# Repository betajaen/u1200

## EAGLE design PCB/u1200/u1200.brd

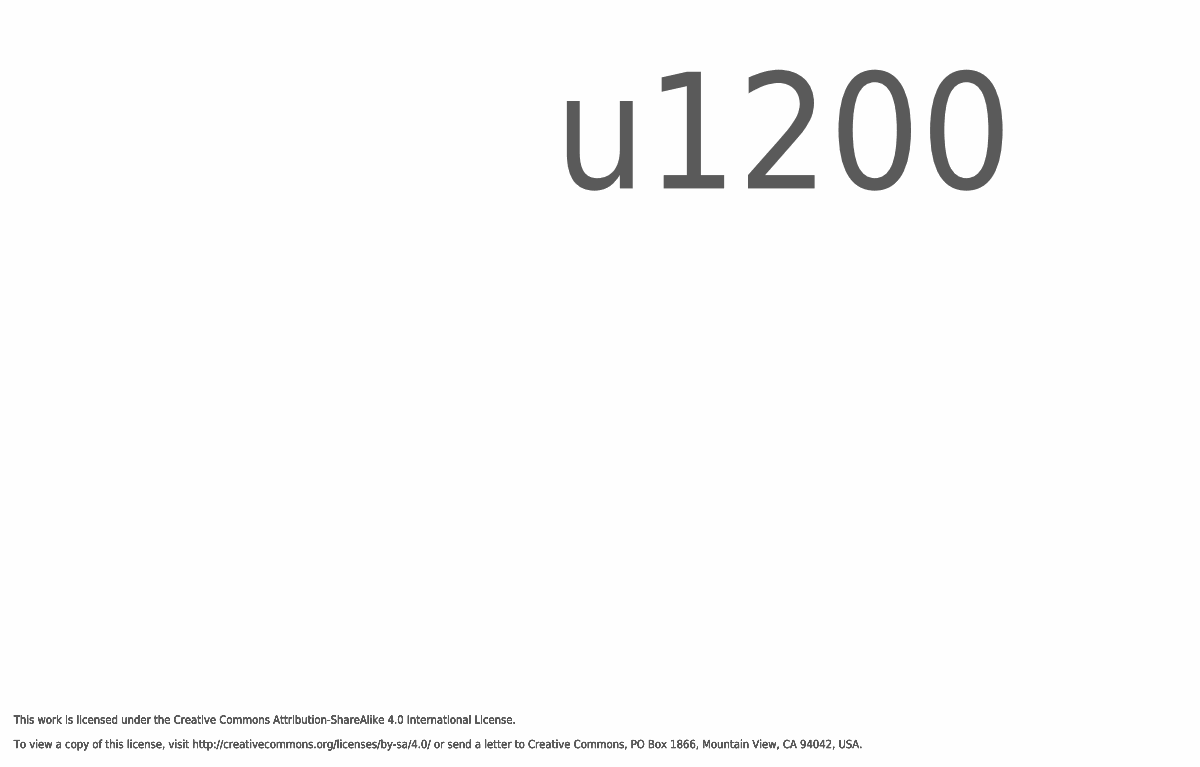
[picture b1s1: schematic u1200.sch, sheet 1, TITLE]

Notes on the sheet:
u1200
This work is licensed under the Creative Commons Attribution-ShareAlike 4.0 International License. To view a copy of this license, visit http://creativecommons.org/licenses/by-sa/4.0/ or send a letter to Creative Commons, PO Box 1866, Mountain View, CA 94042, USA.

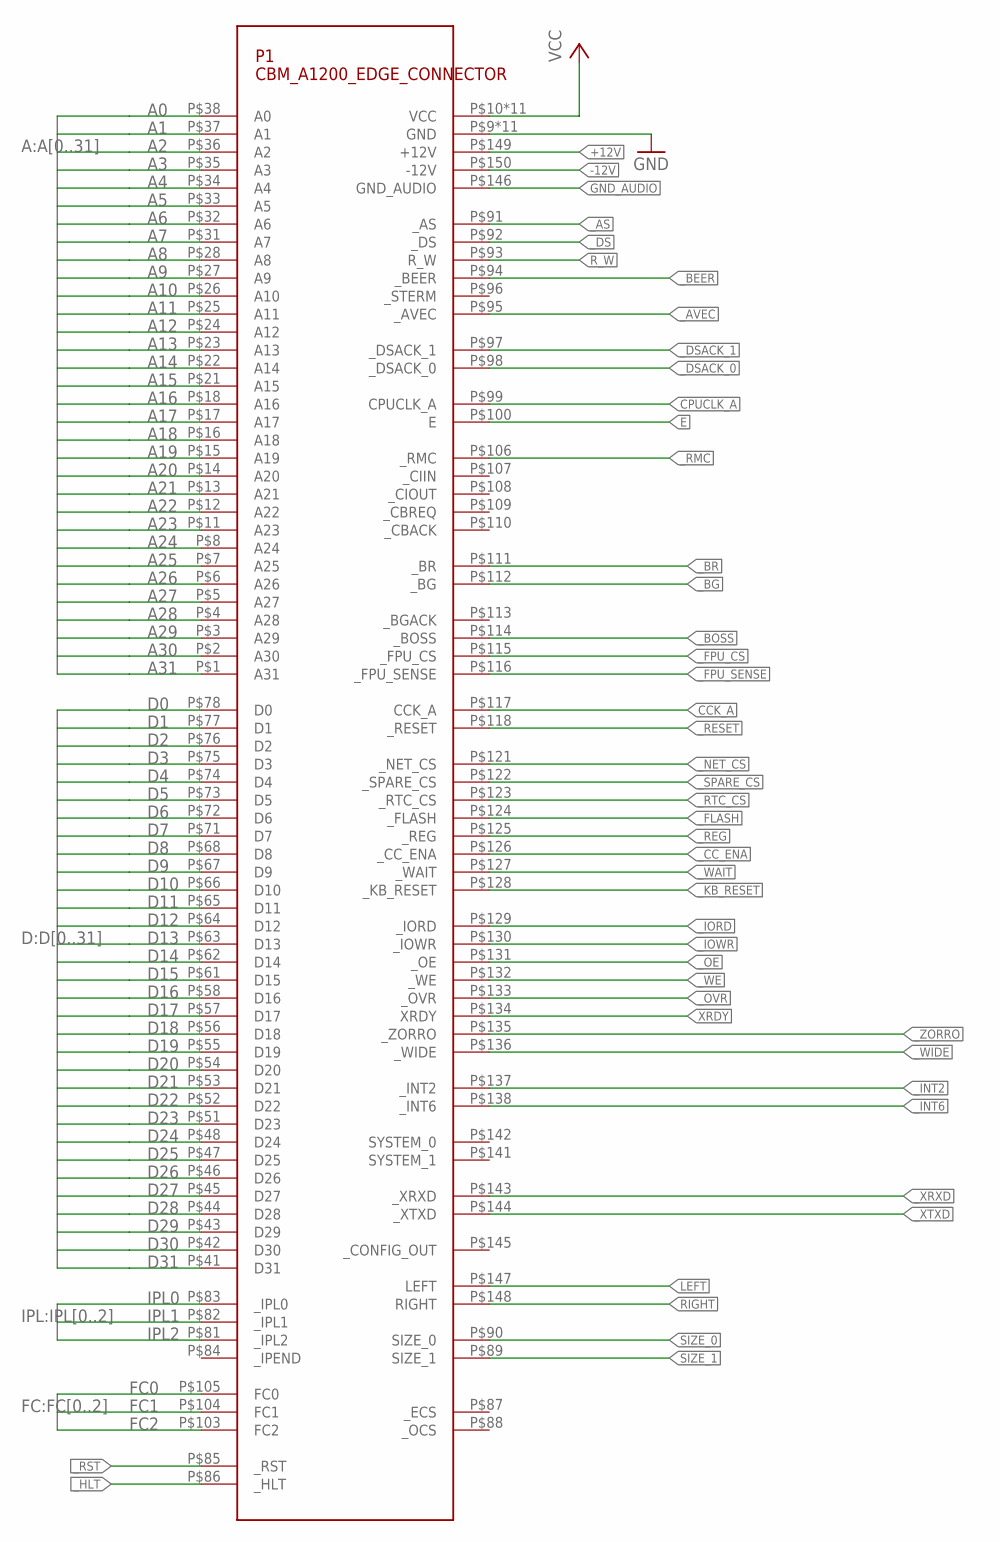
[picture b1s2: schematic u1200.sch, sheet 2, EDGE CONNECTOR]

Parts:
P1: CBM_A1200_EDGE_CONNECTOR; CBM_A1200_EDGE_CONNECTOR_150P

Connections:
+12V: P1.P$149 (+12V); also elsewhere on the board
-12V: P1.P$150 (-12V); also elsewhere on the board
A0: P1.P$38 (A0); also elsewhere on the board
A1: P1.P$37 (A1); also elsewhere on the board
A2: P1.P$36 (A2); also elsewhere on the board
A3: P1.P$35 (A3); also elsewhere on the board
A4: P1.P$34 (A4); also elsewhere on the board
A5: P1.P$33 (A5); also elsewhere on the board
A6: P1.P$32 (A6); also elsewhere on the board
A7: P1.P$31 (A7); also elsewhere on the board
A8: P1.P$28 (A8); also elsewhere on the board
A9: P1.P$27 (A9); also elsewhere on the board
A10: P1.P$26 (A10); also elsewhere on the board
A11: P1.P$25 (A11); also elsewhere on the board
A12: P1.P$24 (A12); also elsewhere on the board
A13: P1.P$23 (A13); also elsewhere on the board
A14: P1.P$22 (A14); also elsewhere on the board
A15: P1.P$21 (A15); also elsewhere on the board
A16: P1.P$18 (A16); also elsewhere on the board
A17: P1.P$17 (A17); also elsewhere on the board
A18: P1.P$16 (A18); also elsewhere on the board
A19: P1.P$15 (A19); also elsewhere on the board
A20: P1.P$14 (A20); also elsewhere on the board
A21: P1.P$13 (A21)
A22: P1.P$12 (A22)
A23: P1.P$11 (A23)
A24: P1.P$8 (A24)
A25: P1.P$7 (A25)
A26: P1.P$6 (A26)
A27: P1.P$5 (A27)
A28: P1.P$4 (A28)
A29: P1.P$3 (A29)
A30: P1.P$2 (A30)
A31: P1.P$1 (A31)
CCK_A: P1.P$117 (CCK_A); also elsewhere on the board
CPUCLK_A: P1.P$99 (CPUCLK_A); also elsewhere on the board
D0: P1.P$78 (D0); also elsewhere on the board
D1: P1.P$77 (D1); also elsewhere on the board
D2: P1.P$76 (D2); also elsewhere on the board
D3: P1.P$75 (D3); also elsewhere on the board
D4: P1.P$74 (D4); also elsewhere on the board
D5: P1.P$73 (D5); also elsewhere on the board
D6: P1.P$72 (D6); also elsewhere on the board
D7: P1.P$71 (D7); also elsewhere on the board
D8: P1.P$68 (D8); also elsewhere on the board
D9: P1.P$67 (D9); also elsewhere on the board
D10: P1.P$66 (D10); also elsewhere on the board
D11: P1.P$65 (D11); also elsewhere on the board
D12: P1.P$64 (D12); also elsewhere on the board
D13: P1.P$63 (D13); also elsewhere on the board
D14: P1.P$62 (D14); also elsewhere on the board
D15: P1.P$61 (D15); also elsewhere on the board
D16: P1.P$58 (D16); also elsewhere on the board
D17: P1.P$57 (D17); also elsewhere on the board
D18: P1.P$56 (D18); also elsewhere on the board
D19: P1.P$55 (D19); also elsewhere on the board
D20: P1.P$54 (D20); also elsewhere on the board
D21: P1.P$53 (D21); also elsewhere on the board
D22: P1.P$52 (D22); also elsewhere on the board
D23: P1.P$51 (D23); also elsewhere on the board
D24: P1.P$48 (D24); also elsewhere on the board
D25: P1.P$47 (D25); also elsewhere on the board
D26: P1.P$46 (D26); also elsewhere on the board
D27: P1.P$45 (D27); also elsewhere on the board
D28: P1.P$44 (D28); also elsewhere on the board
D29: P1.P$43 (D29); also elsewhere on the board
D30: P1.P$42 (D30); also elsewhere on the board
D31: P1.P$41 (D31); also elsewhere on the board
E: P1.P$100 (E)
FC0: P1.P$105 (FC0); also elsewhere on the board
FC1: P1.P$104 (FC1); also elsewhere on the board
FC2: P1.P$103 (FC2); also elsewhere on the board
GND: P1.P$9 (GND), P1.P$19 (GND), P1.P$29 (GND), P1.P$39 (GND), P1.P$49 (GND), P1.P$59 (GND), P1.P$69 (GND), P1.P$79 (GND), P1.P$101 (GND), P1.P$119 (GND), P1.P$139 (GND); also elsewhere on the board
GND_AUDIO: P1.P$146 (GND_AUDIO)
IPL0: P1.P$83 (_IPL0); also elsewhere on the board
IPL1: P1.P$82 (_IPL1); also elsewhere on the board
IPL2: P1.P$81 (_IPL2); also elsewhere on the board
LEFT: P1.P$147 (LEFT)
RIGHT: P1.P$148 (RIGHT)
R_W: P1.P$93 (R_W); also elsewhere on the board
SIZE_0: P1.P$90 (SIZE_0); also elsewhere on the board
SIZE_1: P1.P$89 (SIZE_1); also elsewhere on the board
VCC: P1.P$10 (VCC), P1.P$20 (VCC), P1.P$30 (VCC), P1.P$40 (VCC), P1.P$50 (VCC), P1.P$60 (VCC), P1.P$70 (VCC), P1.P$80 (VCC), P1.P$102 (VCC), P1.P$120 (VCC), P1.P$140 (VCC); also elsewhere on the board
XRDY: P1.P$134 (XRDY); also elsewhere on the board
_AS: P1.P$91 (_AS); also elsewhere on the board
_AVEC: P1.P$95 (_AVEC); also elsewhere on the board
_BEER: P1.P$94 (_BEER); also elsewhere on the board
_BG: P1.P$112 (_BG)
_BOSS: P1.P$114 (_BOSS)
_BR: P1.P$111 (_BR); also elsewhere on the board
_CC_ENA: P1.P$126 (_CC_ENA)
_DS: P1.P$92 (_DS); also elsewhere on the board
_DSACK_0: P1.P$98 (_DSACK_0); also elsewhere on the board
_DSACK_1: P1.P$97 (_DSACK_1); also elsewhere on the board
_FLASH: P1.P$124 (_FLASH)
_FPU_CS: P1.P$115 (_FPU_CS)
_FPU_SENSE: P1.P$116 (_FPU_SENSE)
_HLT: P1.P$86 (_HLT); also elsewhere on the board
_INT2: P1.P$137 (_INT2); also elsewhere on the board
_INT6: P1.P$138 (_INT6); also elsewhere on the board
_IORD: P1.P$129 (_IORD)
_IOWR: P1.P$130 (_IOWR)
_KB_RESET: P1.P$128 (_KB_RESET)
_NET_CS: P1.P$121 (_NET_CS)
_OE: P1.P$131 (_OE); also elsewhere on the board
_OVR: P1.P$133 (_OVR); also elsewhere on the board
_REG: P1.P$125 (_REG)
_RESET: P1.P$118 (_RESET)
_RMC: P1.P$106 (_RMC)
_RST: P1.P$85 (_RST); also elsewhere on the board
_RTC_CS: P1.P$123 (_RTC_CS)
_SPARE_CS: P1.P$122 (_SPARE_CS)
_WAIT: P1.P$127 (_WAIT)
_WE: P1.P$132 (_WE); also elsewhere on the board
_WIDE: P1.P$136 (_WIDE); also elsewhere on the board
_XRXD: P1.P$143 (_XRXD)
_XTXD: P1.P$144 (_XTXD)
_ZORRO: P1.P$135 (_ZORRO); also elsewhere on the board

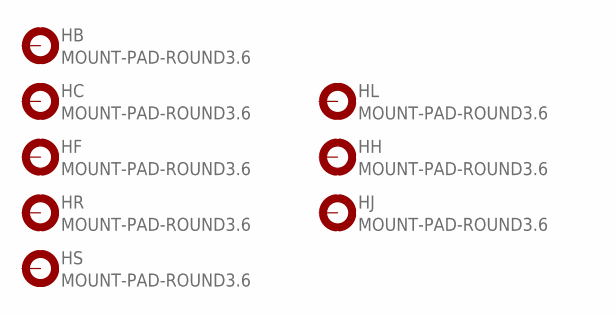
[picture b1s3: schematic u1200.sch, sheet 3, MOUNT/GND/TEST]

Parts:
HB: MOUNT-PAD-ROUND3.6; 3,6-PAD
HC: MOUNT-PAD-ROUND3.6; 3,6-PAD
HF: MOUNT-PAD-ROUND3.6; 3,6-PAD
HH: MOUNT-PAD-ROUND3.6; 3,6-PAD
HJ: MOUNT-PAD-ROUND3.6; 3,6-PAD
HL: MOUNT-PAD-ROUND3.6; 3,6-PAD
HR: MOUNT-PAD-ROUND3.6; 3,6-PAD
HS: MOUNT-PAD-ROUND3.6; 3,6-PAD

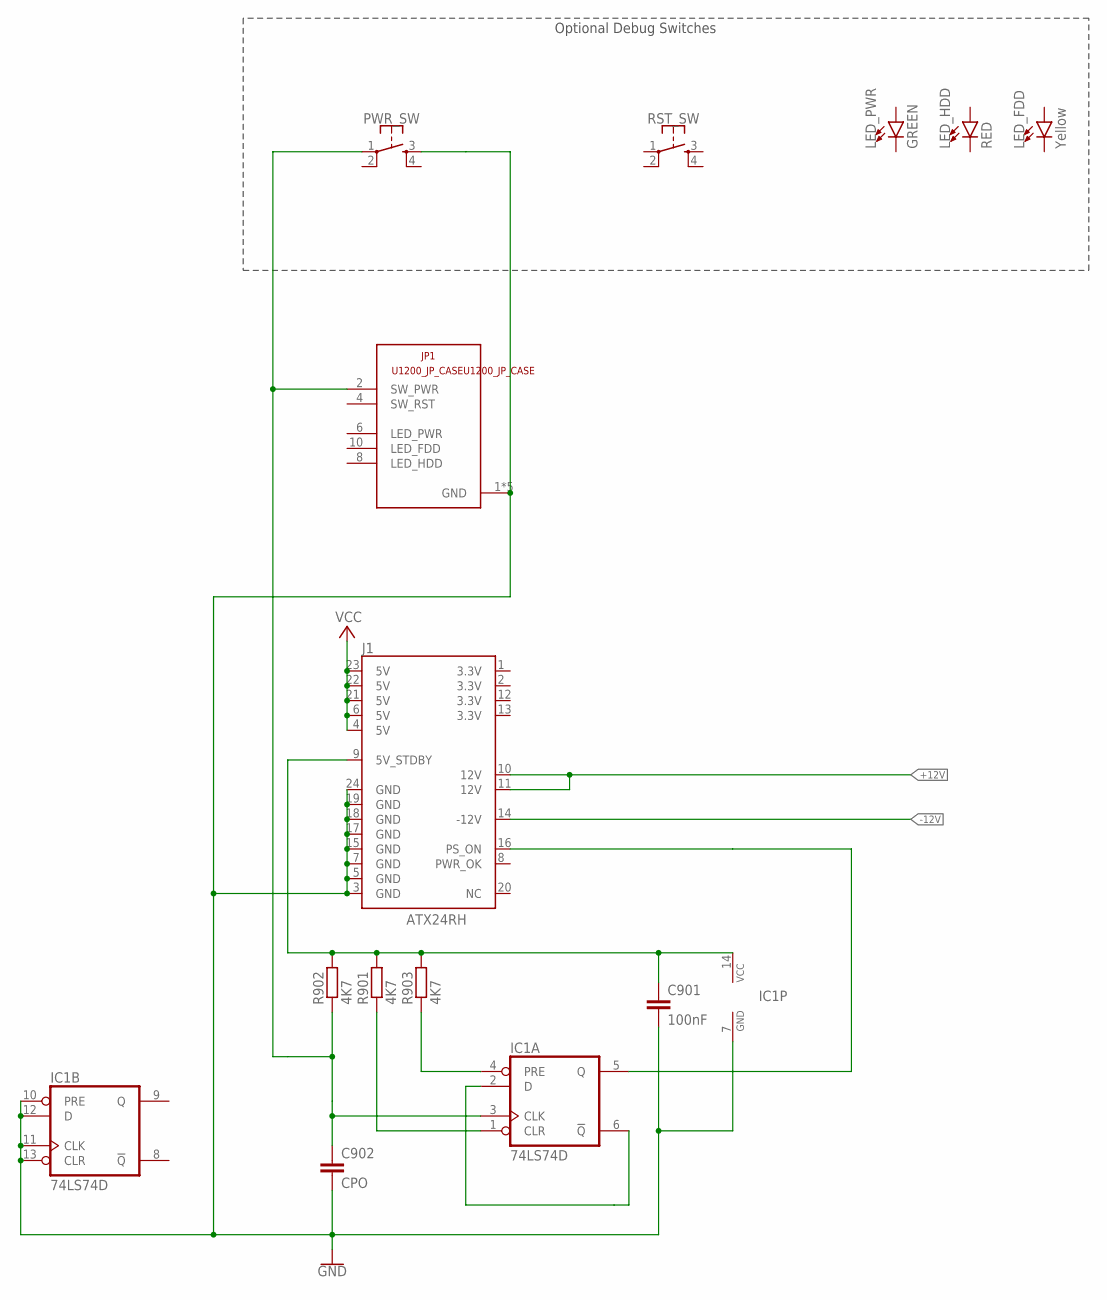
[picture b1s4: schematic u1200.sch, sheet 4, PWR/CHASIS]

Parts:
C901: 100nF; C0805
C902: CPO; C0805
IC1: 74LS74D; SO14
J1: ATX24RH; ATX24_RIGHT_ANGLE
JP1: U1200_JP_CASEU1200_JP_CASE; U1200_PINHEAD_2X05_ANNOTATED
LED_FDD: Yellow; LED-0603
LED_HDD: RED; LED-0603
LED_PWR: GREEN; LED-0603
PWR_SW: MOMENTARY-SWITCH-SPST-2-SMD-4.6X2.8MM; TACTILE_SWITCH_SMD_4.6X2.8MM
R901, R902, R903: 4K7; R0805
RST_SW: MOMENTARY-SWITCH-SPST-2-SMD-4.6X2.8MM; TACTILE_SWITCH_SMD_4.6X2.8MM

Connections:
+12V: J1.10 (12V), J1.11 (12V); also elsewhere on the board
-12V: J1.14 (-12V); also elsewhere on the board
GND: C901.2, C902.2, IC1.7 (GND), IC1.10 (PRE), IC1.11 (CLK), IC1.12 (D), IC1.13 (CLR), J1.3 (GND), J1.5 (GND), J1.7 (GND), J1.15 (GND), J1.17 (GND), J1.18 (GND), J1.19 (GND), J1.24 (GND), JP1.1 (GND), JP1.3 (GND), JP1.5 (GND), JP1.7 (GND), JP1.9 (GND), PWR_SW.3; also elsewhere on the board
unnamed: C901.1, IC1.14 (VCC), J1.9 (5V_STDBY), R901.2, R902.2, R903.2
unnamed: IC1.5 (Q), J1.16 (PS_ON)
unnamed: IC1.4 (PRE), R903.1
unnamed: IC1.2 (D), IC1.6 (!Q)
unnamed: IC1.1 (CLR), R901.1
unnamed: C902.1, IC1.3 (CLK), JP1.2 (SW_PWR), PWR_SW.1, R902.1
VCC: J1.4 (5V), J1.6 (5V), J1.21 (5V), J1.22 (5V), J1.23 (5V); also elsewhere on the board

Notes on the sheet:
Optional Debug Switches

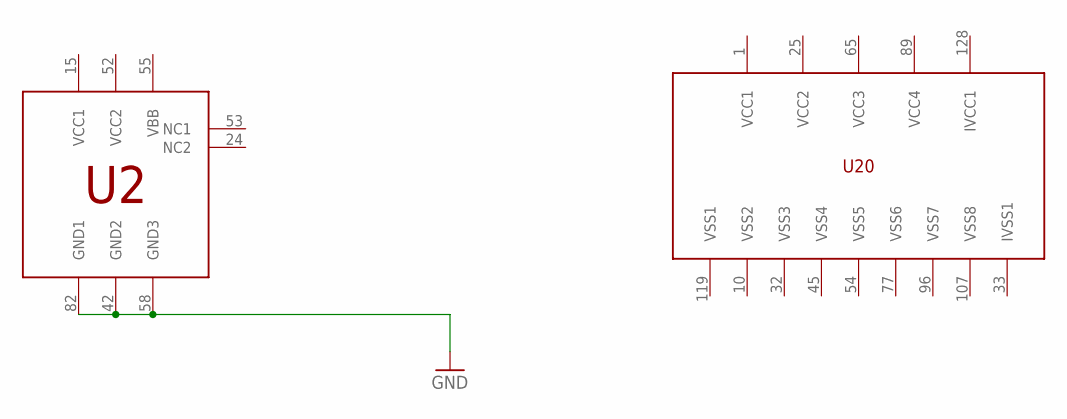
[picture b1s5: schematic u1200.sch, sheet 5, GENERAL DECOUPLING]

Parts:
U2: CBM_8374; PLCC84-SMD-AMP-SOCKED
U20: CBM_391425; SQFP-S-28X28-128

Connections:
GND: U2.42 (GND2), U2.58 (GND3), U2.82 (GND1); also elsewhere on the board
VBB: U2.55 (VBB)
VCC1: U2.15 (VCC1); also elsewhere on the board
VCC2: U2.52 (VCC2); also elsewhere on the board

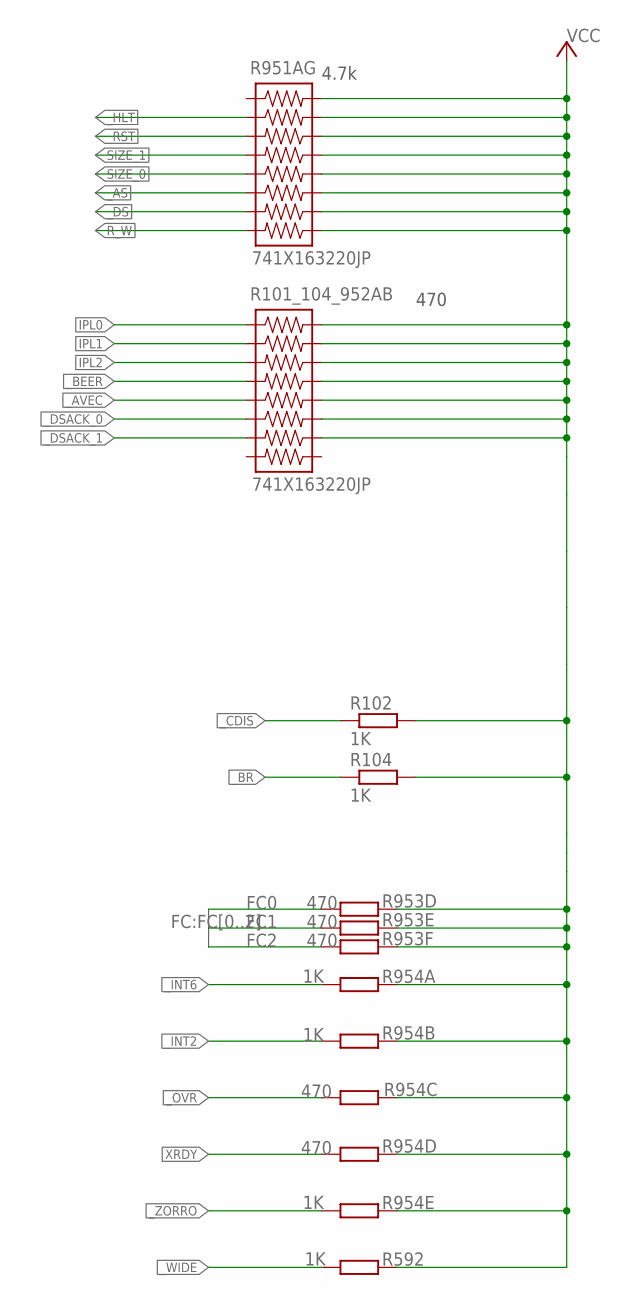
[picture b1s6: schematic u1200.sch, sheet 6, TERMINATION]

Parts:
R101_104_952AB: 741X163220JP; MPN 741X163471JP; DIGIKEY_PARTNO 741X163471JPTR-ND
R102, R104, R592, R954A, R954B, R954E: 1K; R0805
R951AG: 741X163220JP; MPN 746X101472JP; DIGIKEY_PARTNO 746X101472JPTR-ND
R953D, R953E, R953F, R954C, R954D: 470; R0805

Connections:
FC0: R953D.1; also elsewhere on the board
FC1: R953E.1; also elsewhere on the board
FC2: R953F.1; also elsewhere on the board
IPL0: R101_104_952AB.1; also elsewhere on the board
IPL1: R101_104_952AB.2; also elsewhere on the board
IPL2: R101_104_952AB.3; also elsewhere on the board
R_W: R951AG.8; also elsewhere on the board
SIZE_0: R951AG.5; also elsewhere on the board
SIZE_1: R951AG.4; also elsewhere on the board
VCC: R101_104_952AB.10, R101_104_952AB.11, R101_104_952AB.12, R101_104_952AB.13, R101_104_952AB.14, R101_104_952AB.15, R101_104_952AB.16, R102.2, R104.2, R592.2, R951AG.9, R951AG.10, R951AG.11, R951AG.12, R951AG.13, R951AG.14, R951AG.15, R951AG.16, R953D.2, R953E.2, R953F.2, R954A.2, R954B.2, R954C.2, R954D.2, R954E.2; also elsewhere on the board
XRDY: R954D.1; also elsewhere on the board
_AS: R951AG.6; also elsewhere on the board
_AVEC: R101_104_952AB.5; also elsewhere on the board
_BEER: R101_104_952AB.4; also elsewhere on the board
_BR: R104.1; also elsewhere on the board
_CDIS: R102.1
_DS: R951AG.7; also elsewhere on the board
_DSACK_0: R101_104_952AB.6; also elsewhere on the board
_DSACK_1: R101_104_952AB.7; also elsewhere on the board
_HLT: R951AG.2; also elsewhere on the board
_INT2: R954B.1; also elsewhere on the board
_INT6: R954A.1; also elsewhere on the board
_OVR: R954C.1; also elsewhere on the board
_RST: R951AG.3; also elsewhere on the board
_WIDE: R592.1; also elsewhere on the board
_ZORRO: R954E.1; also elsewhere on the board

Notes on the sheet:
4.7k
470

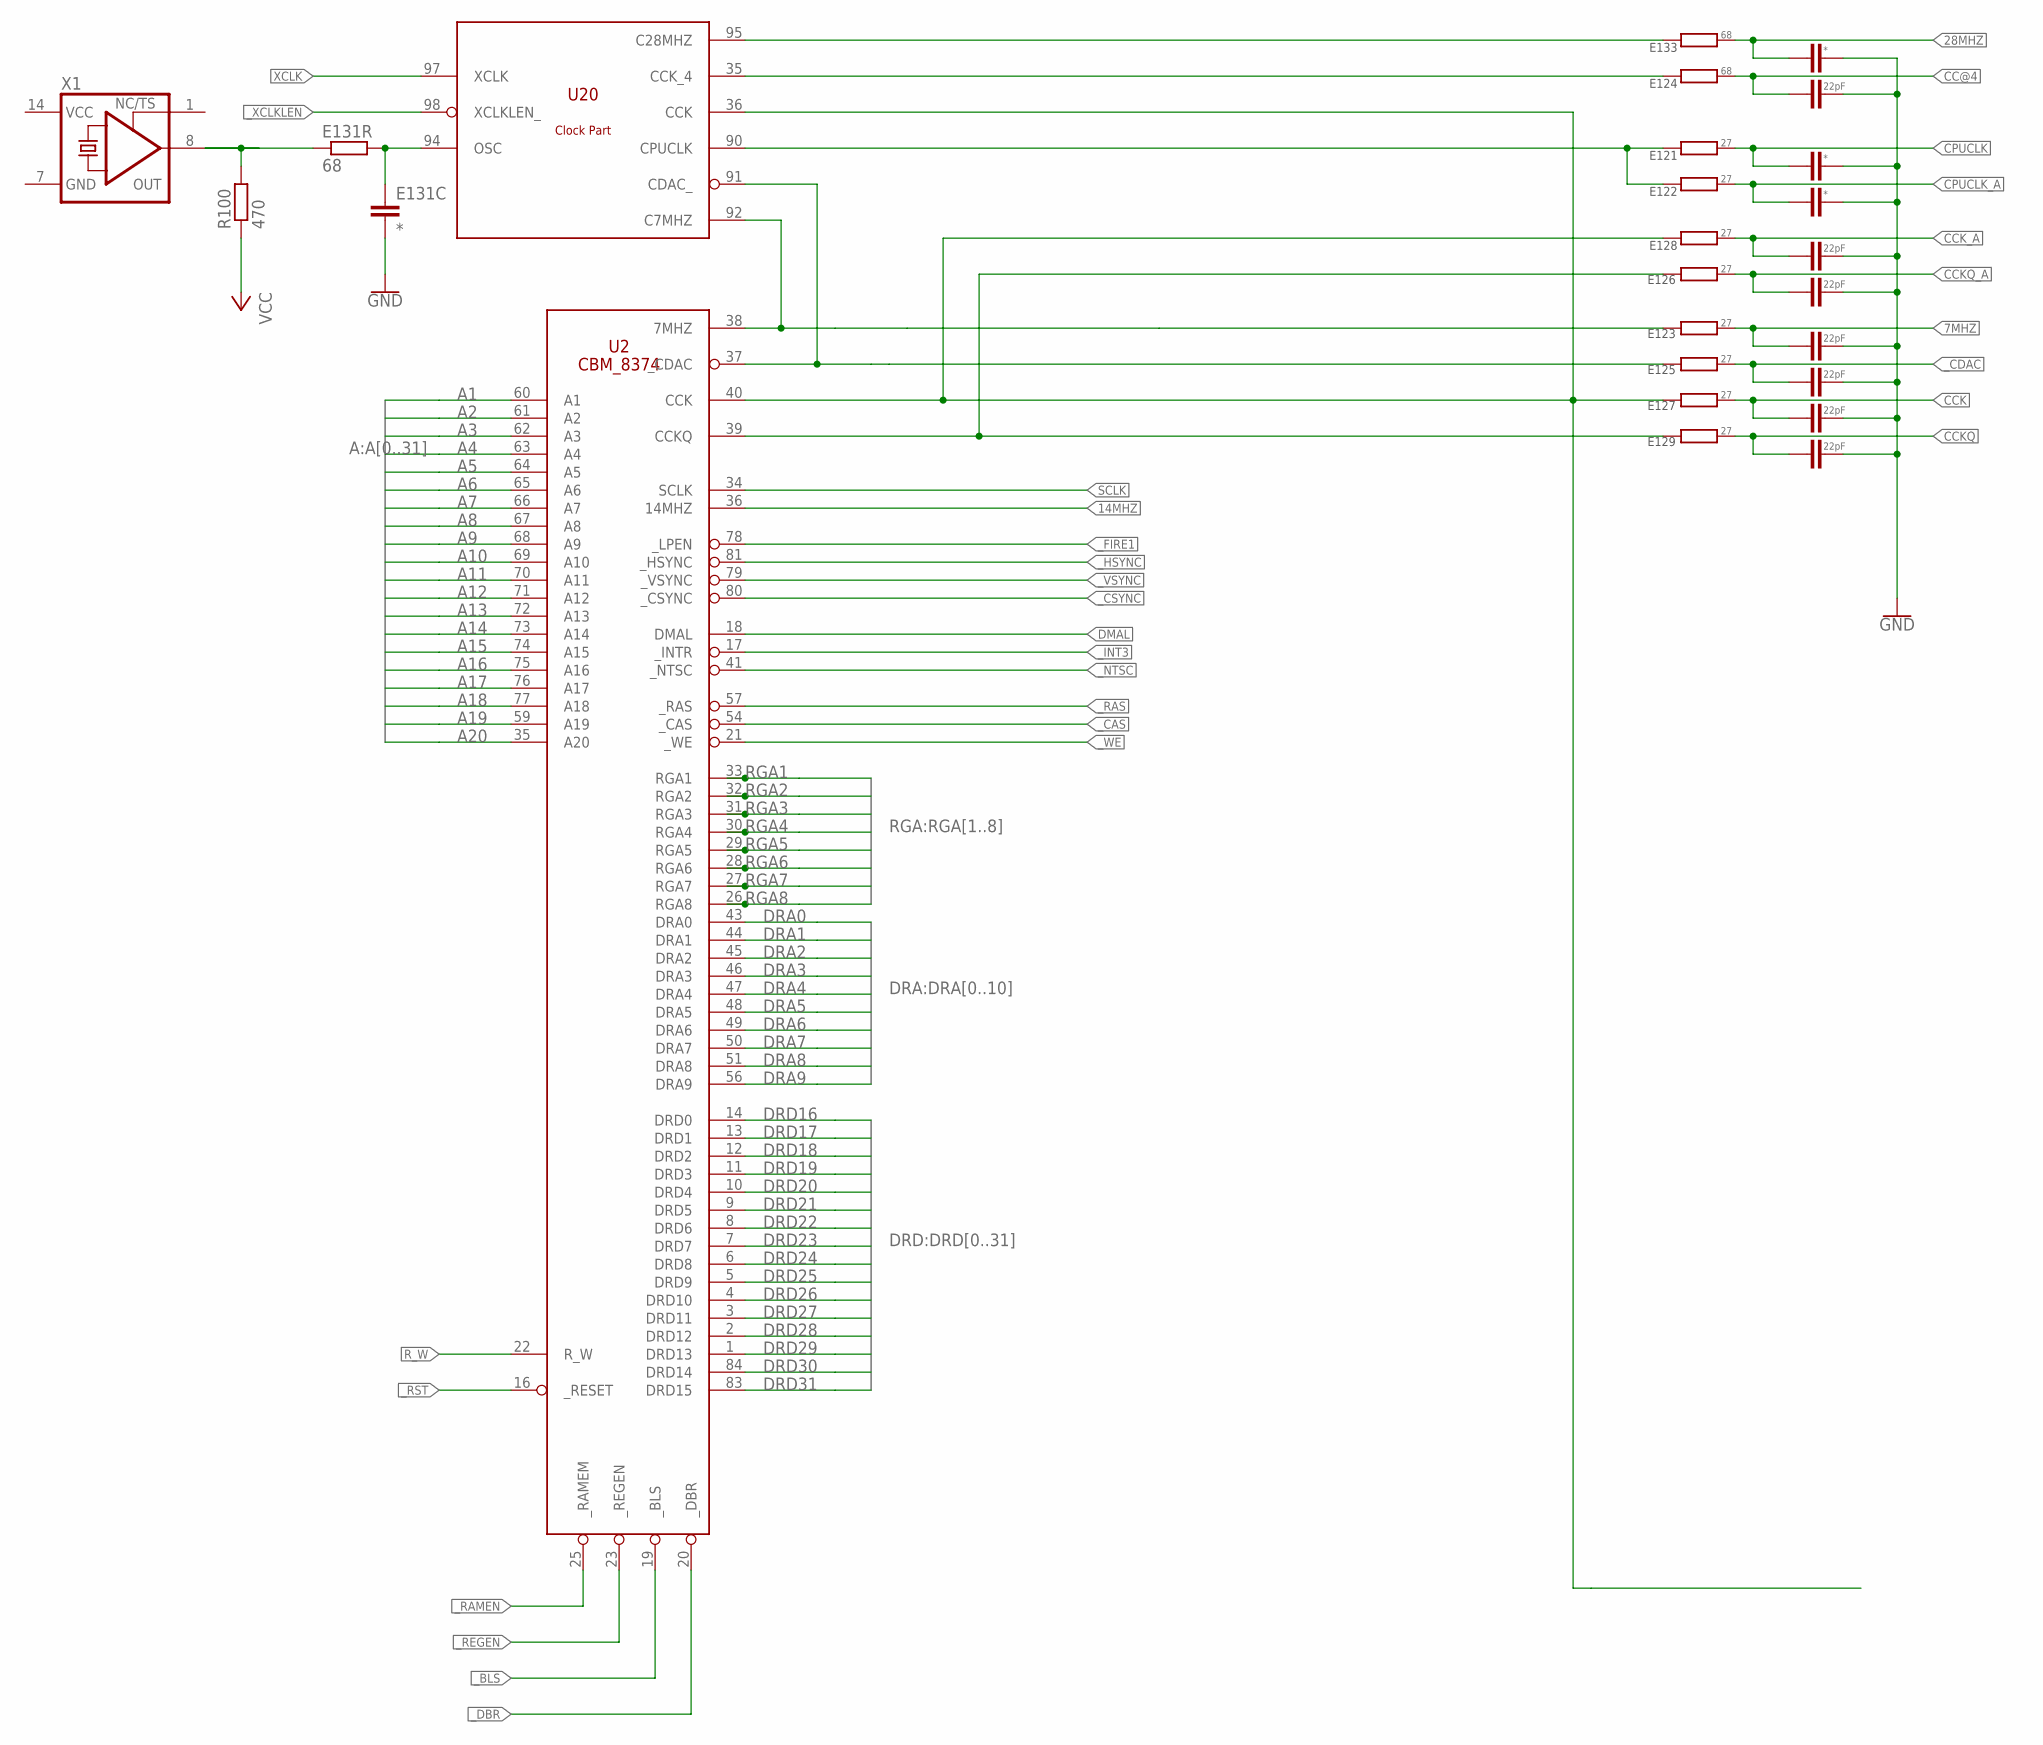
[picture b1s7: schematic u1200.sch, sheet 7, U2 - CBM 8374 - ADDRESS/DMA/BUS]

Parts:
E121C, E122C, E131C, E133C: *; C0805
E121R, E122R, E123R, E125R, E126R, E127R, E128R, E129R: 27; R0805
E123C, E124C, E125C, E126C, E127C, E128C, E129C: 22pF; C0805
E124R, E131R, E133R: 68; R0805
R100: 470; R0805
U2: CBM_8374; PLCC84-SMD-AMP-SOCKED
U20: CBM_391425; SQFP-S-28X28-128
X1: XO-14; DIL14S

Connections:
7MHZ: E123C.1, E123R.1, E123R.2, U2.38 (7MHZ), U20.92 (C7MHZ)
14MHZ: U2.36 (14MHZ); also elsewhere on the board
28MHZ: E133C.1, E133R.2
A1: U2.60 (A1); also elsewhere on the board
A2: U2.61 (A2); also elsewhere on the board
A3: U2.62 (A3); also elsewhere on the board
A4: U2.63 (A4); also elsewhere on the board
A5: U2.64 (A5); also elsewhere on the board
A6: U2.65 (A6); also elsewhere on the board
A7: U2.66 (A7); also elsewhere on the board
A8: U2.67 (A8); also elsewhere on the board
A9: U2.68 (A9); also elsewhere on the board
A10: U2.69 (A10); also elsewhere on the board
A11: U2.70 (A11); also elsewhere on the board
A12: U2.71 (A12); also elsewhere on the board
A13: U2.72 (A13); also elsewhere on the board
A14: U2.73 (A14); also elsewhere on the board
A15: U2.74 (A15); also elsewhere on the board
A16: U2.75 (A16); also elsewhere on the board
A17: U2.76 (A17); also elsewhere on the board
A18: U2.77 (A18); also elsewhere on the board
A19: U2.59 (A19); also elsewhere on the board
A20: U2.35 (A20); also elsewhere on the board
C28MHZ: E133R.1, U20.95 (C28MHZ)
CC@4: E124C.1, E124R.2
CCK: E127C.1, E127R.1, E127R.2, E128R.1, U2.40 (CCK), U20.36 (CCK); also elsewhere on the board
CCKQ: E126R.1, E129C.1, E129R.1, E129R.2, U2.39 (CCKQ)
CCKQ_A: E126C.1, E126R.2
CCK_4: E124R.1, U20.35 (CCK_4)
CCK_A: E128C.1, E128R.2; also elsewhere on the board
CPUCLK: E121C.1, E121R.1, E121R.2, E122R.1, U20.90 (CPUCLK)
CPUCLK_A: E122C.1, E122R.2; also elsewhere on the board
DMAL: U2.18 (DMAL)
DRA0: U2.43 (DRA0); also elsewhere on the board
DRA1: U2.44 (DRA1); also elsewhere on the board
DRA2: U2.45 (DRA2); also elsewhere on the board
DRA3: U2.46 (DRA3); also elsewhere on the board
DRA4: U2.47 (DRA4); also elsewhere on the board
DRA5: U2.48 (DRA5); also elsewhere on the board
DRA6: U2.49 (DRA6); also elsewhere on the board
DRA7: U2.50 (DRA7); also elsewhere on the board
DRA8: U2.51 (DRA8); also elsewhere on the board
DRA9: U2.56 (DRA9)
DRD16: U2.14 (DRD0); also elsewhere on the board
DRD17: U2.13 (DRD1); also elsewhere on the board
DRD18: U2.12 (DRD2); also elsewhere on the board
DRD19: U2.11 (DRD3); also elsewhere on the board
DRD20: U2.10 (DRD4); also elsewhere on the board
DRD21: U2.9 (DRD5); also elsewhere on the board
DRD22: U2.8 (DRD6); also elsewhere on the board
DRD23: U2.7 (DRD7); also elsewhere on the board
DRD24: U2.6 (DRD8); also elsewhere on the board
DRD25: U2.5 (DRD9); also elsewhere on the board
DRD26: U2.4 (DRD10); also elsewhere on the board
DRD27: U2.3 (DRD11); also elsewhere on the board
DRD28: U2.2 (DRD12); also elsewhere on the board
DRD29: U2.1 (DRD13); also elsewhere on the board
DRD30: U2.84 (DRD14); also elsewhere on the board
DRD31: U2.83 (DRD15); also elsewhere on the board
GND: E121C.2, E122C.2, E123C.2, E124C.2, E125C.2, E126C.2, E127C.2, E128C.2, E129C.2, E131C.2, E133C.2, X1.7 (GND); also elsewhere on the board
unnamed: E131R.1, R100.2, X1.8 (OUT)
unnamed: E131C.1, E131R.2, U20.94 (OSC)
RGA1: U2.33 (RGA1); also elsewhere on the board
RGA2: U2.32 (RGA2); also elsewhere on the board
RGA3: U2.31 (RGA3); also elsewhere on the board
RGA4: U2.30 (RGA4); also elsewhere on the board
RGA5: U2.29 (RGA5); also elsewhere on the board
RGA6: U2.28 (RGA6); also elsewhere on the board
RGA7: U2.27 (RGA7); also elsewhere on the board
RGA8: U2.26 (RGA8); also elsewhere on the board
R_W: U2.22 (R_W); also elsewhere on the board
SCLK: U2.34 (SCLK); also elsewhere on the board
VBB: U2.55 (VBB)
VCC: R100.1, X1.14 (VCC); also elsewhere on the board
VCC1: U2.15 (VCC1); also elsewhere on the board
VCC2: U2.52 (VCC2); also elsewhere on the board
XCLK: U20.97 (XCLK)
_BLS: U2.19 (_BLS)
_CAS: U2.54 (_CAS); also elsewhere on the board
_CDAC: E125C.1, E125R.1, E125R.2, U2.37 (_CDAC), U20.91 (CDAC_)
_CSYNC: U2.80 (_CSYNC); also elsewhere on the board
_DBR: U2.20 (_DBR); also elsewhere on the board
_FIRE1: U2.78 (_LPEN)
_HSYNC: U2.81 (_HSYNC); also elsewhere on the board
_INT3: U2.17 (_INTR)
_NTSC: U2.41 (_NTSC)
_RAMEN: U2.25 (_RAMEM)
_RAS: U2.57 (_RAS); also elsewhere on the board
_REGEN: U2.23 (_REGEN)
_RST: U2.16 (_RESET); also elsewhere on the board
_VSYNC: U2.79 (_VSYNC); also elsewhere on the board
_WE: U2.21 (_WE); also elsewhere on the board
_XCLKLEN: U20.98 (XCLKLEN_)

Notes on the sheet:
E128
E126
E123
E125
E127
E122
E121
E133
E124
E129

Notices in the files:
PCB/u1200/u1200.brd:
CC BY-SA 4.0
parts and their libraries:
SparkFun-Switches: Licensing: Creative Commons ShareAlike 4.0 International - https://creativecommons.org/licenses/by-sa/4.0
